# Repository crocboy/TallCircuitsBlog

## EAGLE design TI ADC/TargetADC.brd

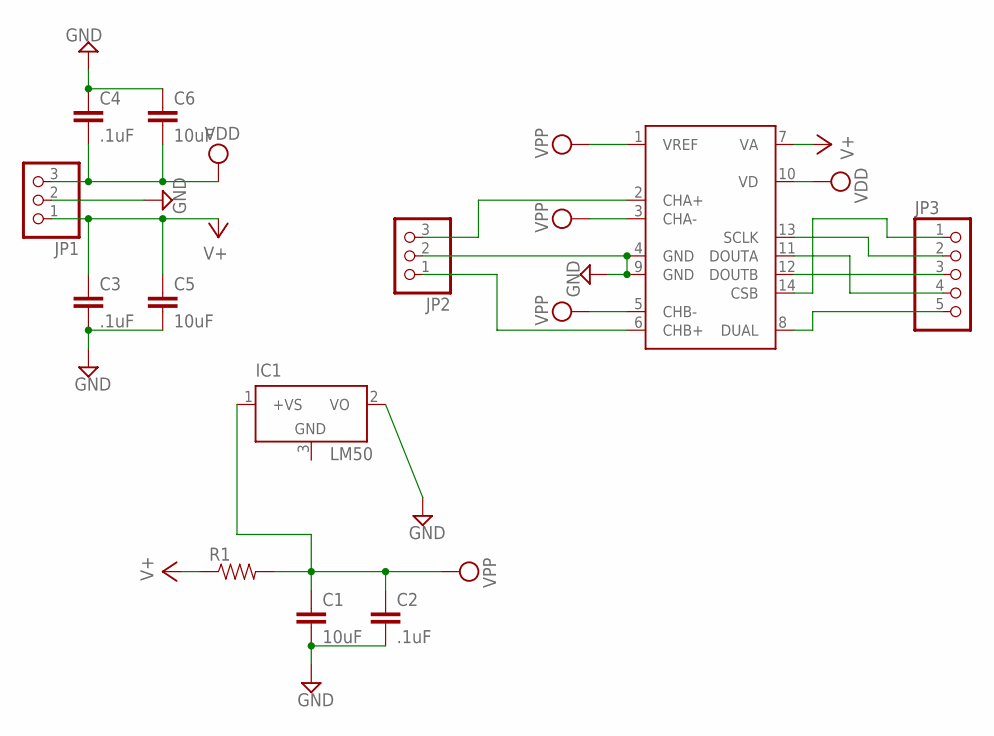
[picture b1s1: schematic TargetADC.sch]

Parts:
C1, C5, C6: 10uF; 0805
C2, C3, C4: .1uF; 0805
IC1: LM50; SOT23
JP1, JP2: PINHD-1X3; 1X03
JP3: PINHD-1X5; 1X05
R1: RESISTOR0805-RES; 0805
U1: ADC122S706; TSSOP14

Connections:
GND: C1.2, C2.2, C3.2, C4.1, C5.2, C6.1, IC1.2 (VO), IC1.3 (GND), JP1.2, JP2.2, U1.4 (GND), U1.9 (GND)
unnamed: JP3.4, U1.11 (DOUTA)
unnamed: JP2.3, U1.2 (CHA+)
unnamed: JP2.1, U1.6 (CHB+)
unnamed: JP3.3, U1.12 (DOUTB)
unnamed: JP3.2, U1.13 (SCLK)
unnamed: JP3.1, U1.14 (CSB)
unnamed: JP3.5, U1.8 (DUAL)
V+: C3.1, C5.1, JP1.1, R1.1, U1.7 (VA)
VDD: C4.2, C6.2, JP1.3, U1.10 (VD)
VPP: C1.1, C2.1, IC1.1 (+VS), R1.2, U1.1 (VREF), U1.3 (CHA-), U1.5 (CHB-)

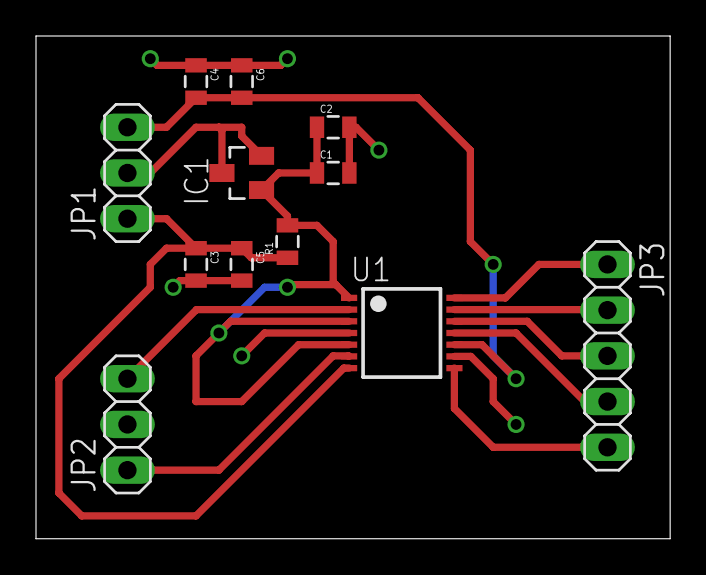
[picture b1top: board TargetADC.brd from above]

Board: 2 copper layers, 35.2 x 27.9 mm, 12 parts (0 on the bottom side), 11 nets.

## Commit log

2015-08-28 Added ADC eagle files
2015-08-28 Added text LCD files

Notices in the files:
parts and their libraries:
SparkFun-Capacitors: Licensing: Creative Commons ShareAlike 4.0 International - https://creativecommons.org/licenses/by-sa/4.0
